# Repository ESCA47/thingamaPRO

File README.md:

# thingamaPRO

Order at your own risk, even i fuck up too often. Maybe poke at me for help but for the most part you are on your own if you do decide to order these.
This projecet was created to do the stupid thing I wanted and I got mine.

Goals of the project is to give as one to one a switch pro feel for ultimate on a gcc/phob interface. Anything past that is a nice bonus(melee or people calibrating to their own prefrences).

I highly implore you to calibrate either to the 3dp jig(and follow reccommended offsets or test for your own(except cstick that one is pretty bang on already)) or use some octo shell to calibrate before putting circle gates on these as otherwise the sticks will feel like dogshit and that's on you or whoever made you the thingamapro and you should yell at them.

Some things to absolutely not forget when ordering:

Front boards are 0.8mm thick and need gold finish to work at their best, ill probably chuck some of my bstock stuff for cheap on etsy if you dont want to drop 80 on 5 standard assembly boards

Main PCB is 1.2mm thick and you can do the regular finish as none are in the context of contact pads

Warnings aside the files I have supplied are only really a start since I personally dont want to say use this part or that part and tank the stuff i use over multiple designs so you will need a couple bit more brain cells to actually part out the boards properly. 

So for instance you will need to format the position file properly for jlc to be able to read it and also you need to double check all of the parts are on the right orientation(if someone wants to do this for me feel free since even i dont bother and i tinker with it too much). For the bom it should be descript enough that you can figure out the parts from looking at lcsc so have fun there.

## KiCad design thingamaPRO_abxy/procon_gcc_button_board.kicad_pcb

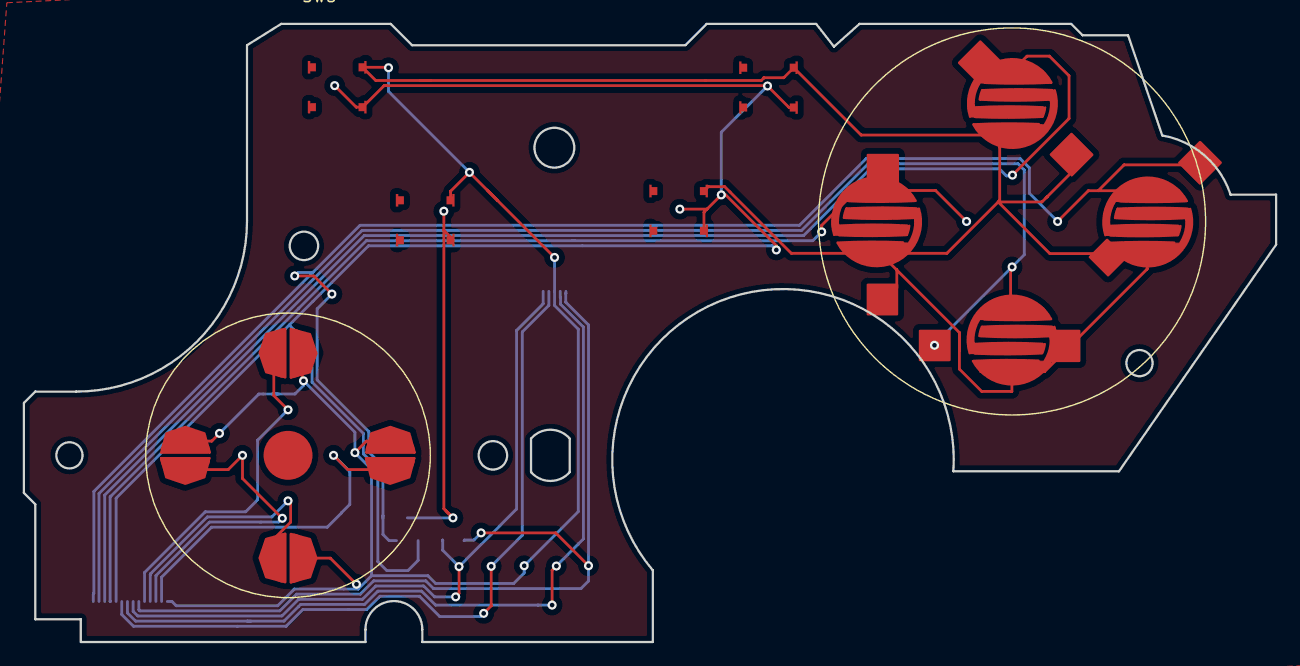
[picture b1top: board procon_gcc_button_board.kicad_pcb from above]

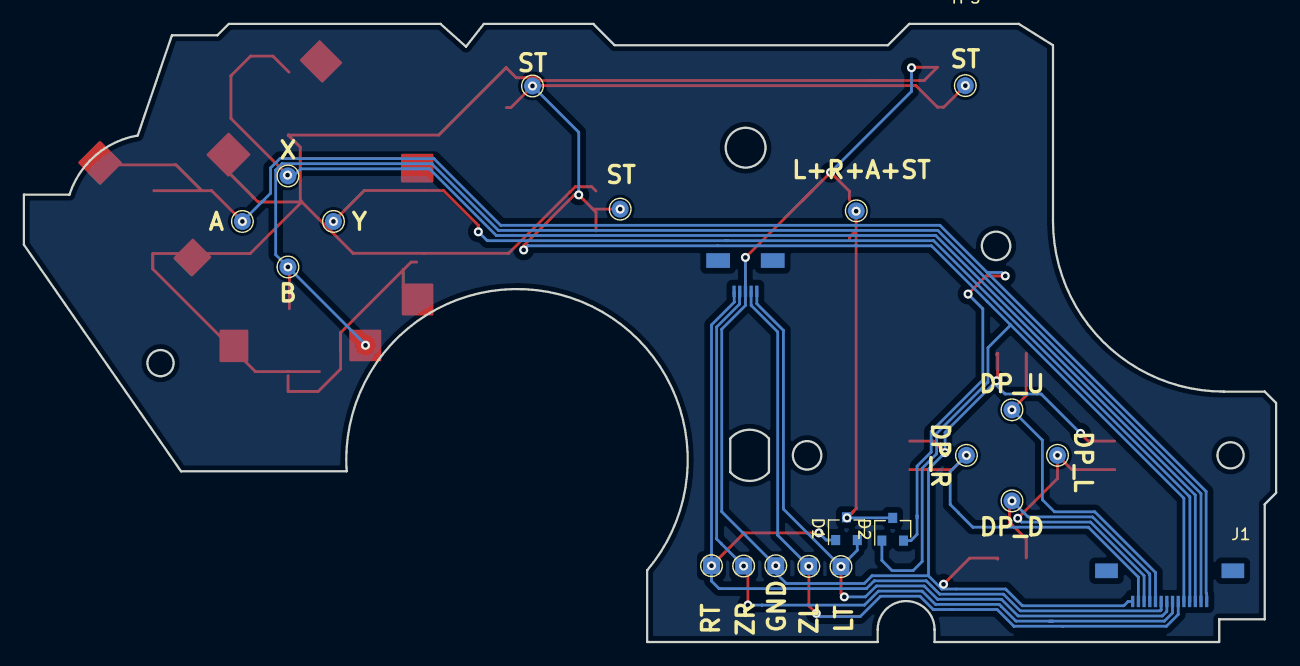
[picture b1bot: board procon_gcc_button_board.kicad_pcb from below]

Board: 2 copper layers, 110.0 x 54.3 mm, 31 parts (21 on the bottom side), 15 nets.

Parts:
D1, D2: BAV70; SOT-23
J1: Button Board; molex_5051101492_14P
J2: bumpers; molex_5051100592_5P
Ref**: Val**; ABXY_Contact_Omron_Switch
Ref**#2, Ref**#3, Ref**#4: Val**; ABXY_Contact_Omron_Switch
SW1: procon_abxy
SW2: procon_dpad
SW3, SW4, SW5, SW6: TL3315NF100Q; TL3315NFxxxQ
TP1, TP2, TP3, TP4, TP5, TP5#2, TP5#3, TP5#4, TP6, TP7, TP8, TP9, TP10, TP11, TP12, TP13, TP14: TestPoint; TestPoint_Pad_D1.5mm

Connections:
BB_BTN_A: D2.2 (A), J1.1, Ref**#4.2, SW1.1 (A), TP1.1
BB_BTN_B: J1.2, Ref**.2, SW1.2 (B), TP2.1
BB_BTN_DP_D: J1.11, SW2.3 (DP_D), TP11.1
BB_BTN_DP_L: J1.12, SW2.4 (DP_L), TP12.1
BB_BTN_DP_R: J1.13, SW2.2 (DP_R), TP13.1
BB_BTN_DP_U: J1.10, SW2.1 (DP_U), TP10.1
BB_BTN_LT: D1.2 (A), J1.8, J2.1, TP8.1
BB_BTN_RT: D1.1 (A), J1.9, J2.5, TP9.1
BB_BTN_ST: D2.1 (A), J1.5, SW3.1, SW5.1, SW6.1, TP5.1, TP5#2.1, TP5#3.1, TP5#4.1
BB_BTN_X: J1.3, SW1.4 (X), TP3.1
BB_BTN_Y: J1.4, SW1.3 (Y), TP4.1
BB_BTN_ZL: J1.6, J2.2, TP6.1
BB_BTN_ZR: J1.7, J2.4, TP7.1
GND: J1.14, J2.3, Ref**#2.2, Ref**#3.2, SW1.GND, SW2.GND, SW3.2, SW4.2, SW5.2, SW6.2, TP14.1
unnamed: D1.3 (K), D2.3 (K), SW4.1

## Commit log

2022-12-23 abxy board kicad files
2022-12-23 main board+license
2022-12-23 made lib
2022-12-23 models+symbols
2022-12-23 adding libraries
2022-12-23 phobgcc+other libs
2022-12-23 phob2 library
2022-12-23 Delete proboss.zip
    wrong gerber that would cause issues i think
2023-02-24 front board changes
2023-02-24 remove backups to clean up thing
2023-02-24 cleaning up prod files for sanity reasons
2023-02-24 prod files removal
2023-02-24 abxy board added
2023-02-24 abxy board bom shell
2023-02-24 made calibration jig folder and documentation
2023-02-24 calibration jig stls
    steps will come eventually
2023-02-24 Main pcb+bom shell/pos files
